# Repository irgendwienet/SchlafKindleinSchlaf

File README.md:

# SchlafKindleinSchlaf

Alternative hardware and software (Arduino based) to control the crystal ball led light to become a slow moving good-night-light for babies instead of a flashing disco light effect.

You can find similar no name / china led effect lights at amazon and ebay. I believe most of them contain the same hardware. I used the following for this experiment: http://www.amazon.de/gp/product/B00EZMMKEI

This hardware replaces the original control circuit and moves the motor much slower and does not flash or does anything exciting. 

TODO: more details etc.

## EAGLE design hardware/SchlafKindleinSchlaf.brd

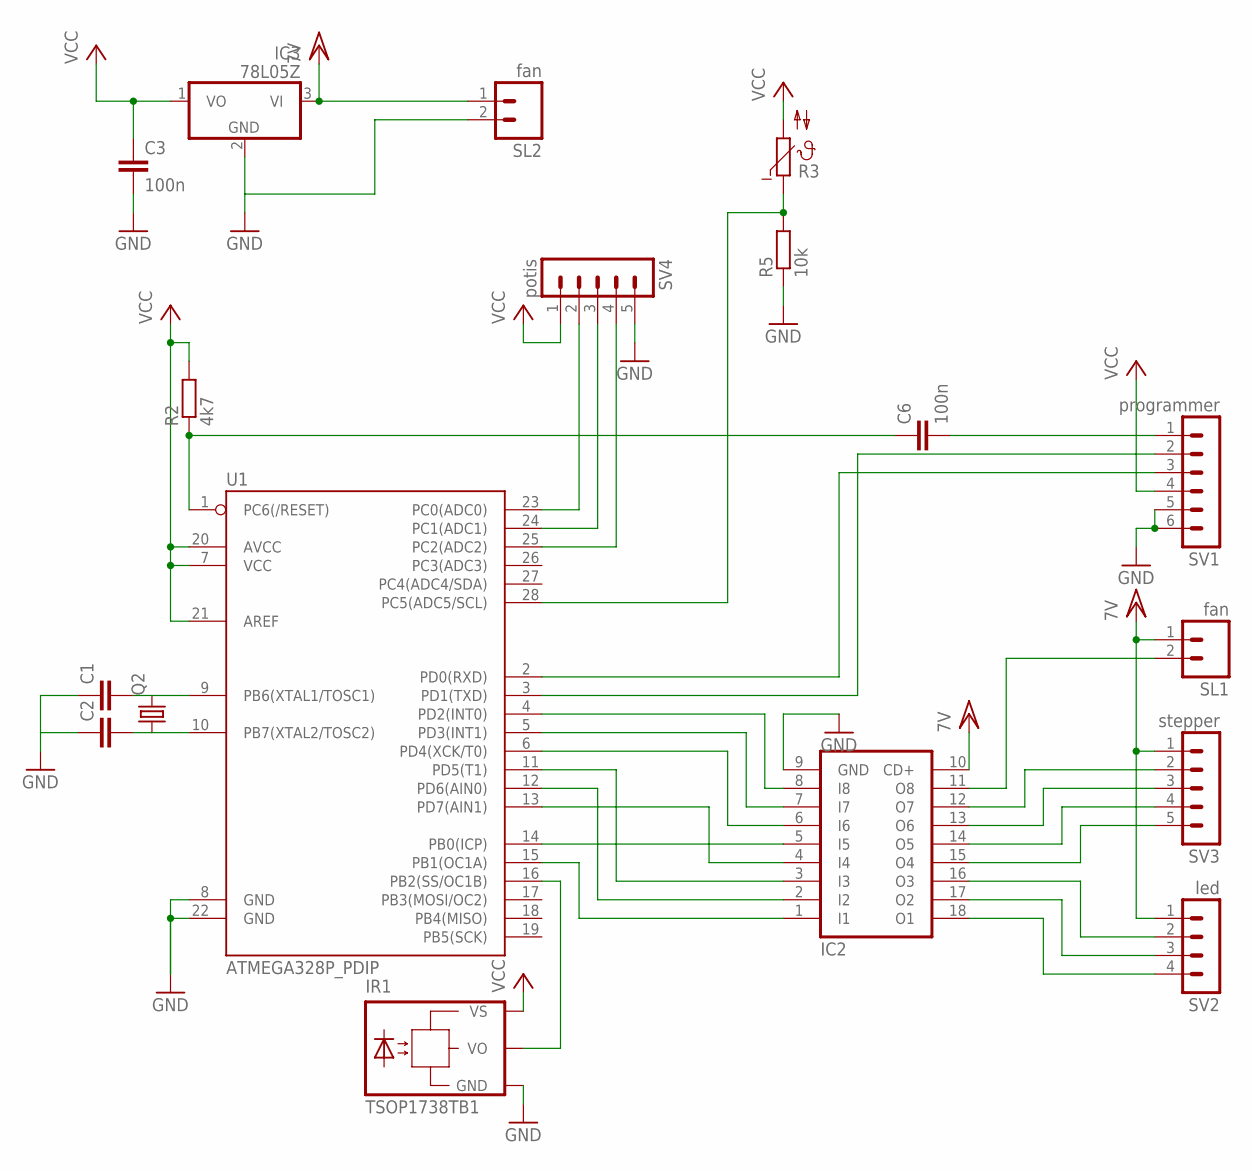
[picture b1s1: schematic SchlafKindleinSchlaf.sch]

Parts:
C1, C2: C2.5/2; C2.5-2
C3, C6: 100n; C2.5-2
IC2: ULN2803A; DIL18
IC3: 78L05Z; TO92
IR1: TSOP1738TB1; TSOP17_TB1
Q2: CRYSTALHC49S; HC49/S
R2: 4k7; 0207/7
R3: NTC640; P640
R5: 10k; 0207/7
SL1, SL2: fan; 02PA
SV1: programmer; MA06-1
SV2: led; MA04-1
SV3: stepper; MA05-1
SV4: potis; MA05-1
U1: ATMEGA328P_PDIP; DIL28-3

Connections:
GND: C1.1, C2.1, C3.2, IC2.9 (GND), IC3.2 (GND), IR1.GND, R5.1, SL2.2, SV1.5, SV1.6, SV4.5, U1.8 (GND), U1.22 (GND)
unnamed: IC2.1 (I1), U1.15 (PB1(OC1A))
unnamed: IC2.2 (I2), U1.12 (PD6(AIN0))
unnamed: C1.2, Q2.2, U1.9 (PB6(XTAL1/TOSC1))
unnamed: C2.2, Q2.1, U1.10 (PB7(XTAL2/TOSC2))
unnamed: IR1.VO, U1.16 (PB2(SS/OC1B))
unnamed: SV1.3, U1.2 (PD0(RXD))
unnamed: SV1.2, U1.3 (PD1(TXD))
unnamed: C6.2, SV1.1
unnamed: C6.1, R2.1, U1.1 (PC6(/RESET))
unnamed: IC2.3 (I3), U1.11 (PD5(T1))
unnamed: IC2.8 (I8), U1.4 (PD2(INT0))
unnamed: IC2.7 (I7), U1.5 (PD3(INT1))
unnamed: IC2.6 (I6), U1.6 (PD4(XCK/T0))
unnamed: IC2.5 (I5), U1.14 (PB0(ICP))
unnamed: IC2.4 (I4), U1.13 (PD7(AIN1))
unnamed: IC2.11 (O8), SL1.2
unnamed: IC2.12 (O7), SV3.2
unnamed: IC2.13 (O6), SV3.3
unnamed: IC2.14 (O5), SV3.4
unnamed: IC2.15 (O4), SV3.5
unnamed: IC2.16 (O3), SV2.2
unnamed: IC2.17 (O2), SV2.3
unnamed: IC2.18 (O1), SV2.4
unnamed: SV4.2, U1.23 (PC0(ADC0))
unnamed: SV4.3, U1.24 (PC1(ADC1))
unnamed: SV4.4, U1.25 (PC2(ADC2))
unnamed: R3.1, R5.2, U1.28 (PC5(ADC5/SCL))
VCC: C3.1, IC3.1 (VO), IR1.VS, R2.2, R3.2, SV1.4, SV4.1, U1.7 (VCC), U1.20 (AVCC), U1.21 (AREF)
VCC/2: IC2.10 (CD+), IC3.3 (VI), SL1.1, SL2.1, SV2.1, SV3.1

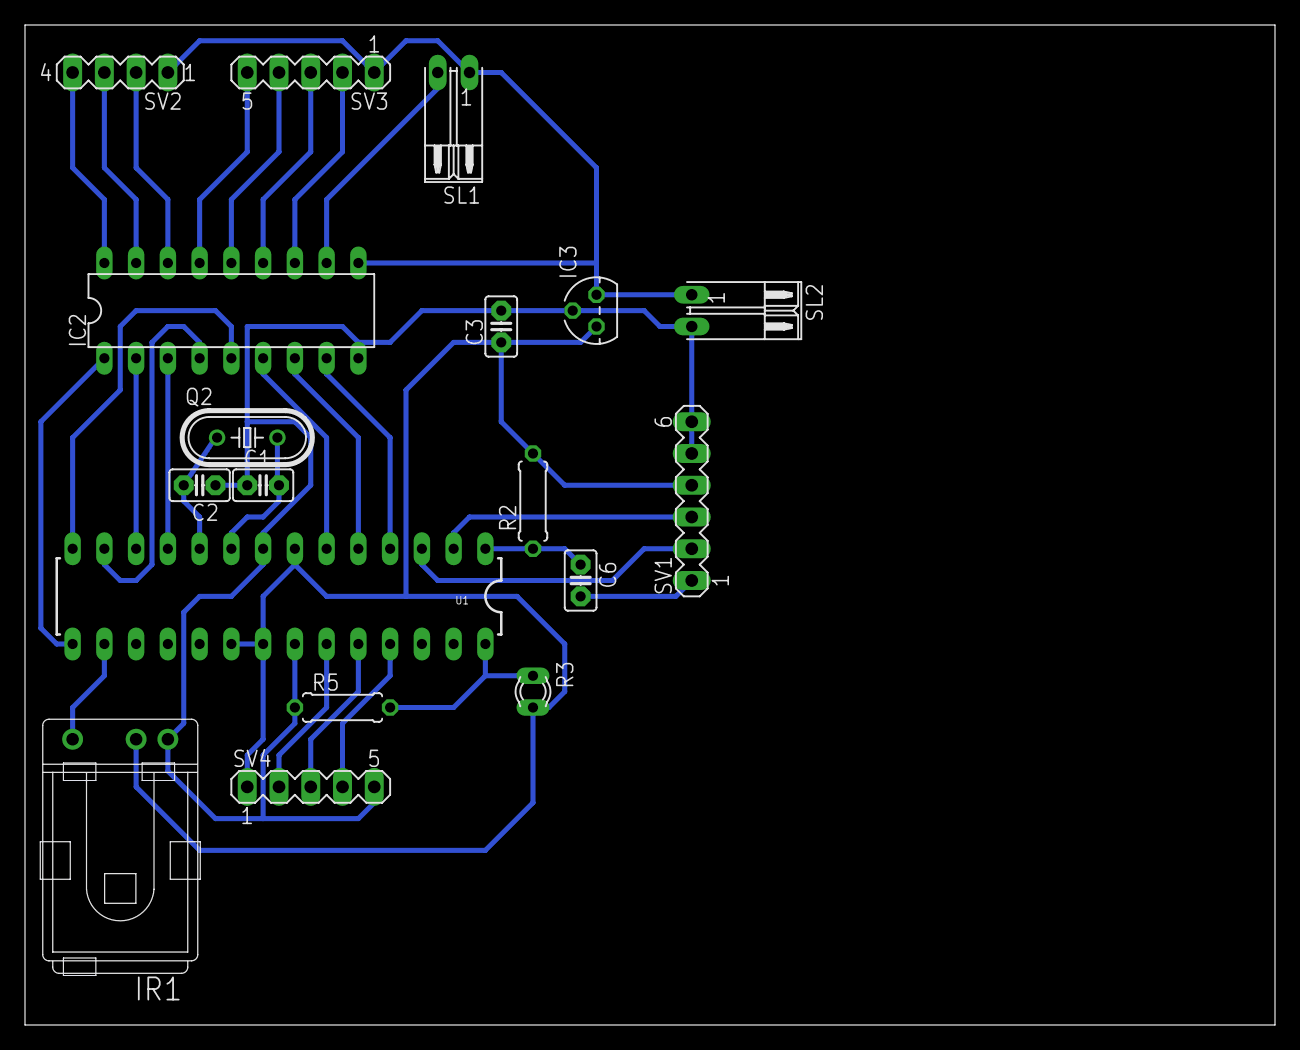
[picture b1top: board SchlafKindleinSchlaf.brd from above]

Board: 2 copper layers, 100.0 x 80.0 mm, 18 parts (0 on the bottom side), 30 nets.

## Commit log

2014-01-04 added my name to license
2014-01-04 readme
2014-01-04 initial checkin

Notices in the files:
parts and their libraries:
SparkFun-DigitalIC: Licensing: CC v3.0 Share-Alike You are welcome to use this library for commercial purposes.
